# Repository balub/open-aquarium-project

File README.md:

This repo is a collection of configs/guides to FOSS tools I use along with all software and hardware I have developed to help me manage and run my aquariums.

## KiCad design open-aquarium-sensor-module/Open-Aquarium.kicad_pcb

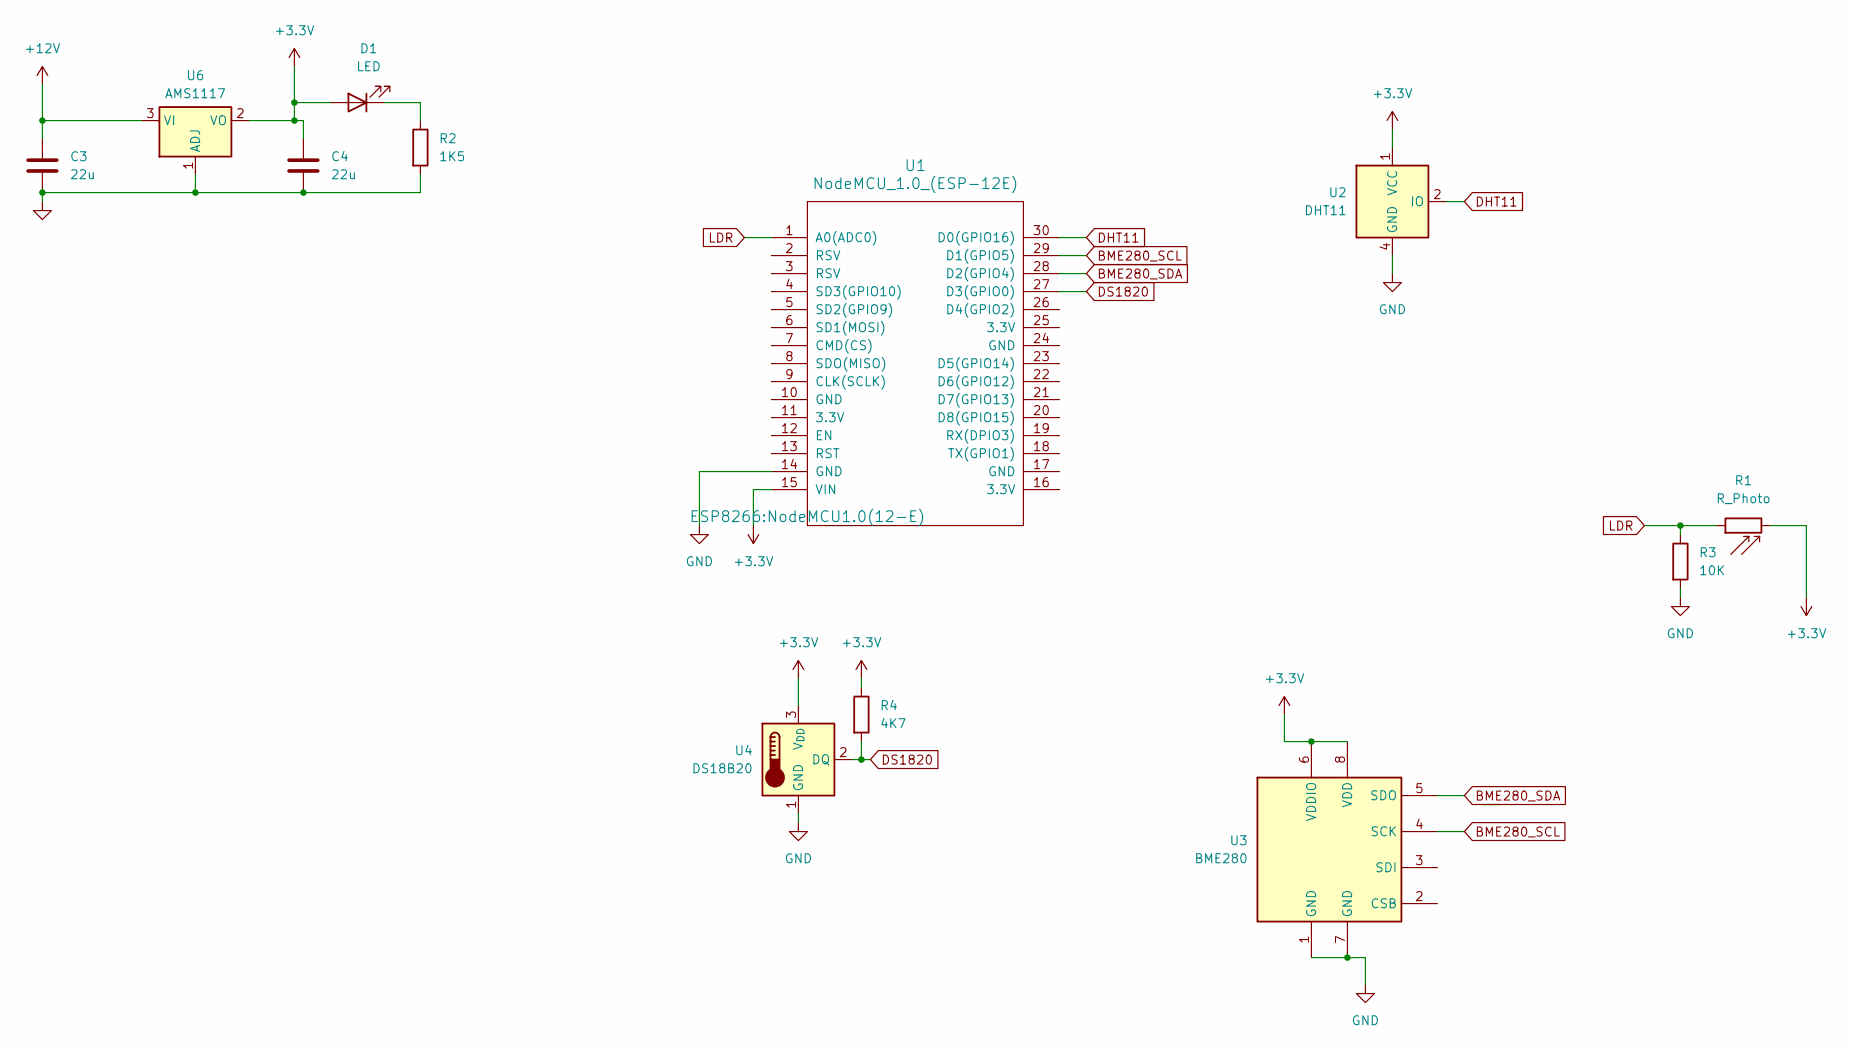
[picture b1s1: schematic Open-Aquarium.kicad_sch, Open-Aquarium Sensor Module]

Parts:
C3, C4: 22u; C_0805_2012Metric
D1: LED; LED_0805_2012Metric
R1: R_Photo; R_Axial_DIN0204_L3.6mm_D1.6mm_P7.62mm_Horizontal
R2: 1K5; R_0402_1005Metric
R3: 10K; R_0402_1005Metric
R4: 4K7; R_0402_1005Metric
U1: NodeMCU_1.0_(ESP-12E); NodeMCU1.0(12-E)
U2: DHT11; Aosong_DHT11_5.5x12.0_P2.54mm
U3: BME280; Bosch_LGA-8_2.5x2.5mm_P0.65mm_ClockwisePinNumbering
U4: DS18B20; TO-92_Inline
U6: AMS1117; SOT-223-3_TabPin2

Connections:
+3.3V: C4.1, D1.2 (A), R1.2, R4.1, U1.15 (VIN), U2.1 (VCC), U3.6 (VDDIO), U3.8 (VDD), U4.3 (V_{DD}), U6.2 (VO)
+12V: C3.1, U6.3 (VI)
BME280_SCL: U1.29 (D1(GPIO5)), U3.4 (SCK)
BME280_SDA: U1.28 (D2(GPIO4)), U3.5 (SDO)
DHT11: U1.30 (D0(GPIO16)), U2.2 (IO)
DS1820: R4.2, U1.27 (D3(GPIO0)), U4.2 (DQ)
GND: C3.2, C4.2, R2.2, R3.2, U1.14 (GND), U2.4 (GND), U3.1 (GND), U3.7 (GND), U4.1 (GND), U6.1 (ADJ)
LDR: R1.1, R3.1, U1.1 (A0(ADC0))
unnamed: D1.1 (K), R2.1

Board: 2 copper layers, 12 parts (0 on the bottom side), 9 nets, no tracks yet.

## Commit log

2023-09-13 chore: initalized project repo
2023-10-03 chore: sensor-module schematic completed and server initalized
